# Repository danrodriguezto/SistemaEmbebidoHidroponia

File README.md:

# **Sistema Embebido para control de cultivo por hidroponia.** #

----
#### Daniel Esteban Rodriguez ####

#### Daniel Santiago Robayo ####

#### María Camila Muñoz Berrio ####

#### Sebastian Ruiz Torres ####

----
## **Descripción del problema** ## 

En la actualidad obtener alimentos vegetales con los nutrientes necesario y sin tanto procesamiento quimico a un valor moderado no es sencillo por lo que la idea de cultivar autonomamente los alimentos en una huerta casera se hace una mejor opción. Ahora, cultivar en la ciudad trae multiples desafios como los son el espacio, el tiempo que es posible dedicarle a esta labor y la falta de conocimiento en esto. De alli nacen vaias alternativas que pretenden reeemplazar las huertas en suelo convencionales por formas más eficientes de cutivar en el mismo espacio y por un valor menor.

Las principales alternativas son: Acuaponía, aeroponía e hidroponía. Esta ultima fue la elegida para desarrollar el proyecto debido a que esta se desarrolla en el agua, esto quiere decir que la raíz se desarrolla en un sustrato o en la misma solución liquida nutritiva utilizada.

## **Propuesta** ##
Se plantea construir un cultivo vertical de hidroponia que reduzca el espacio utilizado para un cultivo y que cuente con un sistema de monitoreo que cuente con sensores previamente calibrados que midan variables importantes para el sostenimiento del cultivo, estos sensores enviaran información que sera procesada y a partir de esto se enviaran alertas al telefono movil del usuario haciendo así interactivo el proceso de producir su alimento. También se pretende que esta dispositivo pueda ser usado por cualquier persona incluso si no conoce sobre hidroponia por medio de avisos informativos-educativos. 

**Publico objetivo** Personas con interesadas en cultivar en espacios reducidos sin la necesidad de dañar los suelos y aprender sobre cultivos hidroponicos.

**Objetivo General**  Diseño, creacion y aplicacion  de un sistema de monitoreo que permita la optimizacion del cultivo y la interaccion educativa con el usuario.

----
## **Requerimientos** ##
* Medir la temperatura de agua
* Medir el nivel del agua
* Ser ergonomico
* Recirculamiento del agua eficiente

## **Diagrama de bloques del sistema.** ##

En el siguiente diagrama se muestran los diferentes componentes que se plantean implementar en el sistema, en este se pueden observar cada una de las entradas y salidas que se pretenden tener en el sistema. Como interacción principal con el usuario se va a construir un sistema que conecte con el telefono del usuario y lo alerte sobre las condiciones de la planta.

## **Diagrama de caja negra con los modulos del ESP32.** ##

## **Diseño de la placa** ##

El diseño de la PCB fue hecho en el programa KiCad y se presentan los esquematicos a continuación,

Se puede observar la distribución de los pines en el ESP32, la conexión de los sensores y la alimentación para este. Aqui se puede observar la conexión del interruptor de flash para subir el programa. 

Se puede detallar la distribución de los pines para cada sensor, con la respectiva alimentación y tierra.

Aquí se presenta la configuración de la alimentación, el regulador(LT1963a5T-3.3), el octoacoplador(SFH617A-1Z01B) y los Mosfet utilizados (IRF4905).

Esta fue la configuración para los led's utilizados, uno de iniciación y otro de boot. También se encuentran el  interruptor de reset.

De la misma manera se crea el diseño de la PCB de dos caras con medidas de 10cm X 10cm.

Y a continuación se presentan ambas caras de la PCB.
Teniendo la cara frontal:

Y la cara trasera:

Por lo tanto las imagenes de la PCB con sus componentes en 3D.

## **Ensamble** ##

En primera instancia se recibio la PCB, fabricada en JLCPCB Hong Kong.

Luego se procede a conseguir los materiales para ser ensamblados en la PCB.

Y ya luego en el laboratorio de mecatronica se procedio a ensamblar todos los componentes.

## **Resultados** ##

Este esquematico se puede ver en la placa ya con los sensores en la siguiente imágen.

Y el cultivo hidroponico.

Y como producto final se tiene:

## **Brochure** ##

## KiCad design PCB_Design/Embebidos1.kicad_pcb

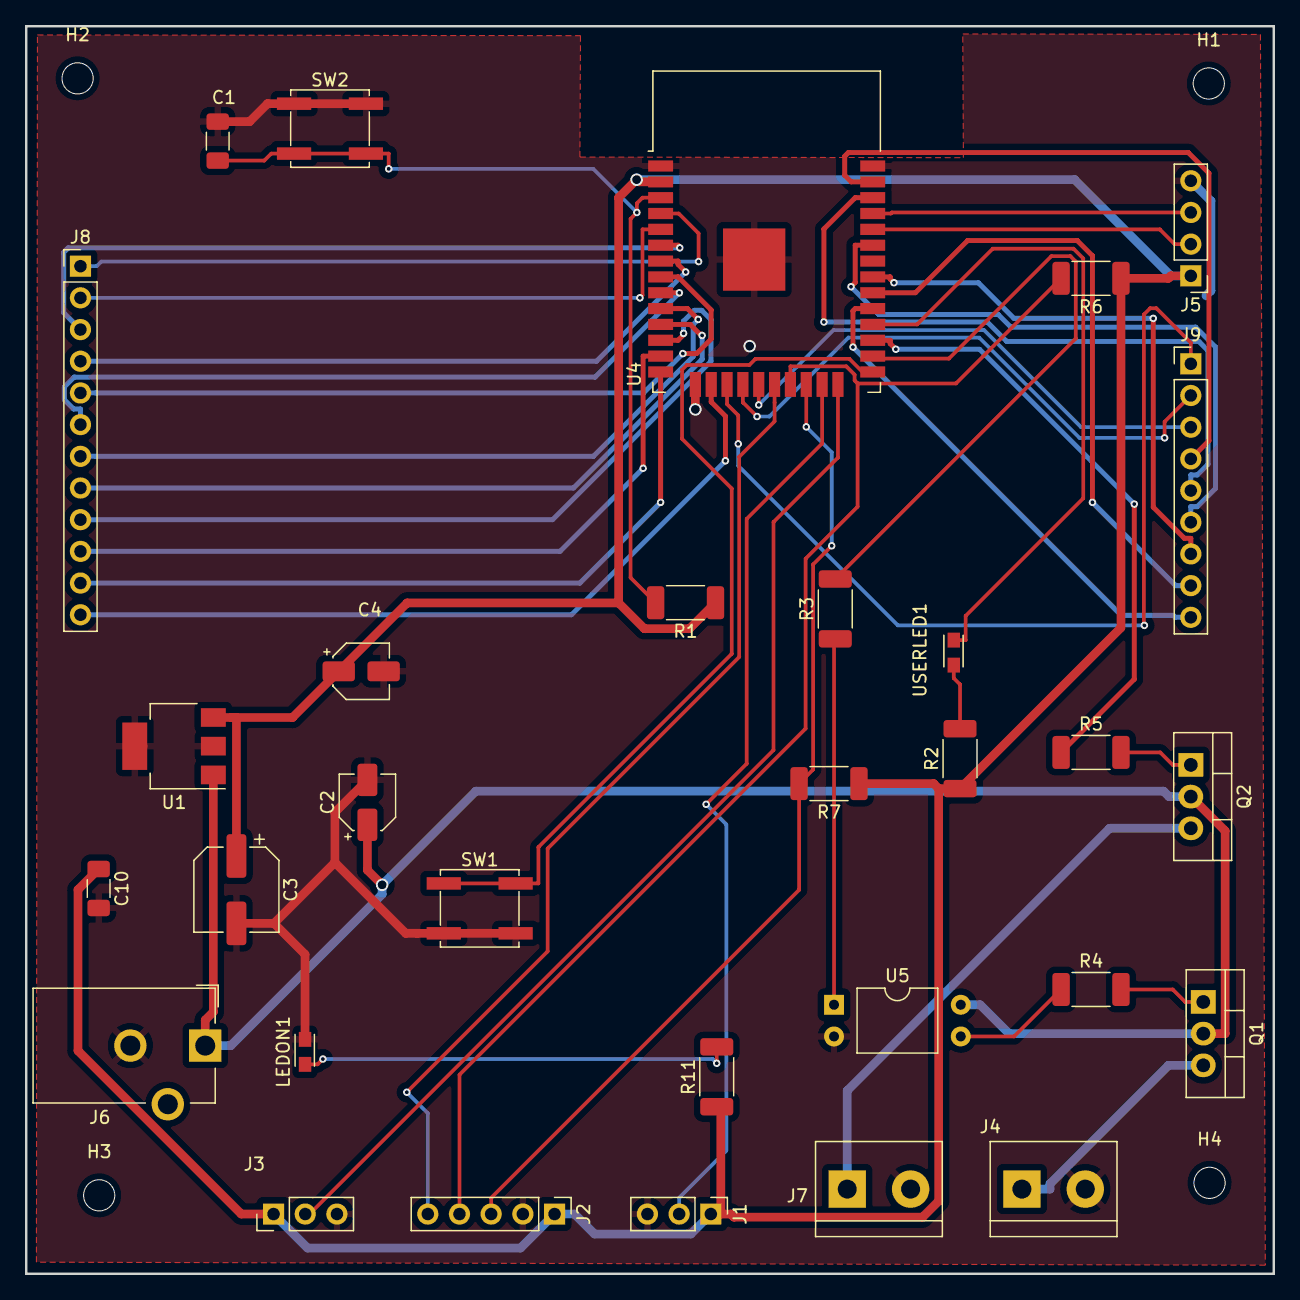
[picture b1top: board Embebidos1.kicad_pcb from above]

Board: 2 copper layers, 100.0 x 100.0 mm, 35 parts (0 on the bottom side), 44 nets.

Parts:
C1, C10: 0.1uF; C_1206_3216Metric_Pad1.33x1.80mm_HandSolder
C2, C4: 10uF; CP_Elec_4x5.4
C3: 100uF; CP_Elec_6.3x7.7
H1, H2, H3, H4: MountingHole; MountingHole_2.5mm
J1: Conn_SensorTemperatura; PinHeader_1x03_P2.54mm_Vertical
J2: Conn_SensorLuz; PinHeader_1x05_P2.54mm_Vertical
J3: Conn_SensorNivelAgua; PinHeader_1x03_P2.54mm_Vertical
J4: Conn_Motor; TerminalBlock_bornier-2_P5.08mm
J5: Conn_Programador; PinHeader_1x04_P2.54mm_Vertical
J6: Jack-DC; BarrelJack_CUI_PJ-102AH_Horizontal
J7: Conn_Luz; TerminalBlock_bornier-2_P5.08mm
J8: Conn_Restantes_1; PinHeader_1x12_P2.54mm_Vertical
J9: Conn_Restantes_2; PinHeader_1x09_P2.54mm_Vertical
LEDON1: LED; LED_miniPLCC_2315_Handsoldering
Q1, Q2: IRF4905; TO-220-3_Vertical
R1, R4, R5: 10k; R_2010_5025Metric_Pad1.40x2.65mm_HandSolder
R2, R3, R11: 220; R_2010_5025Metric_Pad1.40x2.65mm_HandSolder
R6, R7: 2.4k; R_2010_5025Metric_Pad1.40x2.65mm_HandSolder
SW1: SW_Flash; SW_SPST_EVPBF
SW2: SW_Reset; SW_SPST_EVPBF
U1: LT1963AxST-3.3; SOT-223-3_TabPin2
U4: ESP32-WROOM-32
U5: SFH617A-1X016; DIP-4_W10.16mm
USERLED1: LED; LED_miniPLCC_2315_Handsoldering

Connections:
+3V3: C3.1, C4.1, C10.1, J1.1, J2.1, J3.1, J5.1, R1.1, R2.1, R6.1, R7.1, R11.1, U1.3 (OUT), U4.2 (VDD)
+5V: C2.1, J6.1, Q1.2 (D), Q2.2 (D), U1.1 (IN), U5.4
/ACK_LUZ: J2.5, U4.20 (SCK/CLK)
/E32_RST: C1.1, R1.2, SW2.2, U4.3 (EN)
/LED: U4.28 (IO17), USERLED1.1 (K)
/LUZOUT: J7.1, Q2.3 (S)
/LUZPWR: R5.1, U4.27 (IO16)
/MOTOROUT: J4.1, Q1.3 (S)
/MOTORPWR: R3.2, U4.26 (IO4)
/RX: J5.2, U4.34 (RXD0/IO3)
/SCL_LUZ: J2.3, R7.2, U4.22 (SDI/SD1)
/SCS: J9.3, U4.19 (SCS/CMD)
/SDA_LUZ: J2.4, R6.2, U4.21 (SDO/SD0)
/SHD: J9.1, U4.17 (SHD/SD2)
/SNivelAgua: J3.2, U4.24 (IO2)
/STemperatura: J1.2, U4.23 (IO15)
/SWP: J9.2, U4.18 (SWP/SD3)
/Sen_VN: J8.2, U4.5 (SENSOR_VN)
/Sen_VP: J8.1, U4.4 (SENSOR_VP)
/TX: J5.3, U4.35 (TXD0/IO1)
GND: C1.2, C2.2, C3.2, C4.2, C10.2, J1.3, J2.2, J3.3, J4.2, J5.4, J6.2, J7.2, LEDON1.1 (K), SW1.2, SW2.1, U1.2 (GND), U4.1 (GND), U4.15 (GND), U4.38 (GND), U4.39 (GND), U5.2
unnamed: LEDON1.2 (A), R11.2
unnamed: Q1.1 (G), R4.2
unnamed: Q2.1 (G), R5.2
unnamed: R2.2, USERLED1.2 (A)
unnamed: R3.1, U5.1
unnamed: R4.1, U5.3
unnamed: SW1.1, U4.25 (IO0)
unnamed: J8.3, U4.6 (IO34)
unnamed: J8.4, U4.7 (IO35)
unnamed: J8.5, U4.8 (IO32)
unnamed: J8.6, U4.9 (IO33)
unnamed: J8.7, U4.10 (IO25)
unnamed: J8.8, U4.11 (IO26)
unnamed: J8.9, U4.12 (IO27)
unnamed: J8.10, U4.13 (IO14)
unnamed: J8.11, U4.14 (IO12)
unnamed: J8.12, U4.16 (IO13)
unnamed: J9.9, U4.29 (IO5)
unnamed: J9.8, U4.30 (IO18)
unnamed: J9.7, U4.31 (IO19)
unnamed: J9.6, U4.33 (IO21)
unnamed: J9.5, U4.36 (IO22)
unnamed: J9.4, U4.37 (IO23)

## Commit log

2022-08-31 Create Archivo1
2022-11-06 PCB
    PCB
2022-11-08 Costos
    Costos
2022-12-07 Create Imágenes
2022-12-07 Create ESP32
